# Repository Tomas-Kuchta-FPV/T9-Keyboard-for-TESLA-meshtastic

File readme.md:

# T9 Keyboard for TESLA meshtastic
> This is an experimental, low-polish project and without docs.  
It’s shared for reference and tinkering, not as a ready-to-build design.  
Proceed only if you’re comfortable filling in the gaps yourself.  

It's a sub part for an undocumented project that I'm calling TESLA meshtastic.  
Its main purpuse is to find out if a T9 style (4x3) keyboard can be used as a text input for meshtastic.  
The idea is boroved from Travel Buddy. As this idea still lies in my head.  
    
## TESLA meshtastic
Features:
- Speaker with volume control
- T9 style keyboard
- navigation button
- USB-A powered
- Eink?

## Arduino nano code
It should interface the 3x4 keyboard to I2C.

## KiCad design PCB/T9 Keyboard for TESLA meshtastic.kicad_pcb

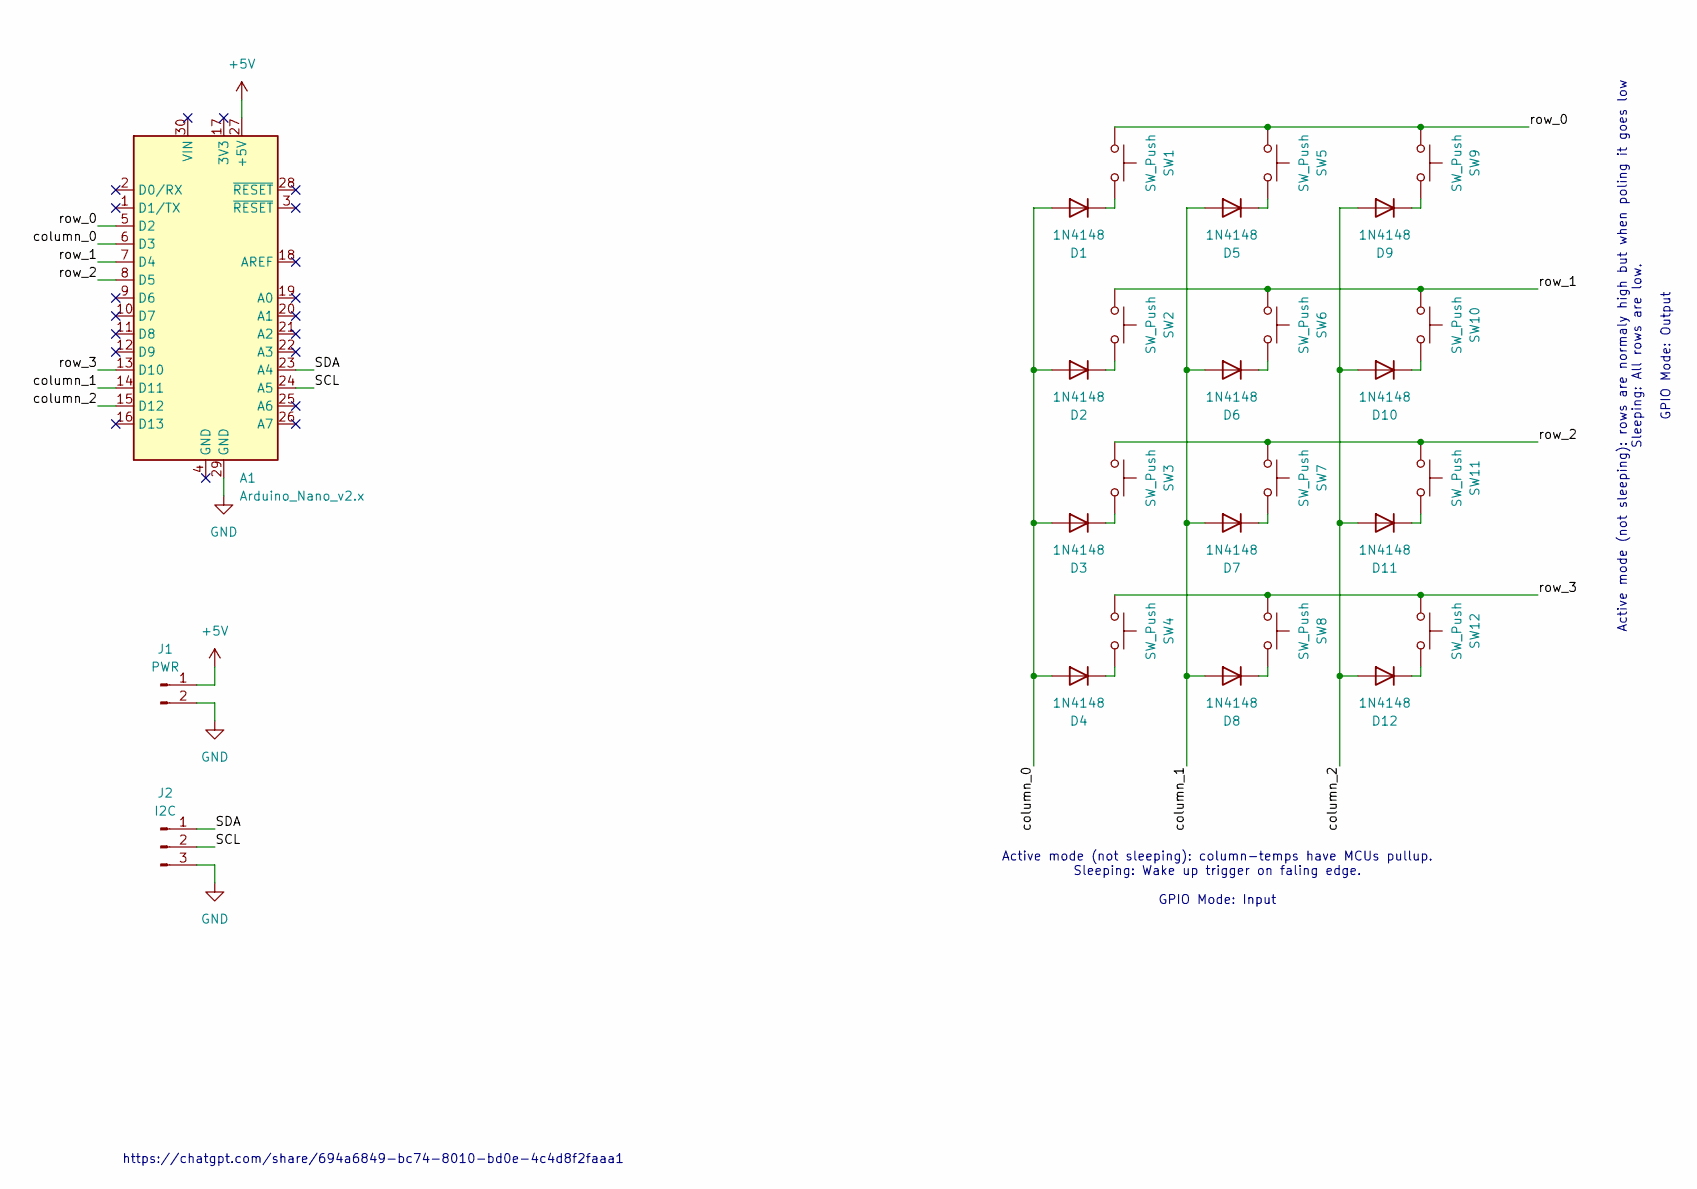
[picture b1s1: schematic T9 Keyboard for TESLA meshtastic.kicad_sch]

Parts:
A1: Arduino_Nano_v2.x; Arduino_Nano
D1, D2, D3, D4, D5, D6, D7, D8, D9, D10, D11, D12: 1N4148; D_DO-35_SOD27_P7.62mm_Horizontal; LCSC C60580
J1: PWR; PinSocket_1x02_P2.54mm_Vertical
J2: I2C; PinSocket_1x03_P2.54mm_Vertical
SW1, SW2, SW3, SW4, SW5, SW6, SW7, SW8, SW9, SW10, SW11, SW12: SW_Push; TESLA-3 FK 573 00; LCSC C318884

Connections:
+5V: A1.27 (+5V), J1.1
/SCL: A1.24 (A5), J2.2
/SDA: A1.23 (A4), J2.1
/column_0: A1.6 (D3), D1.2 (A), D2.2 (A), D3.2 (A), D4.2 (A)
/column_1: A1.14 (D11), D5.2 (A), D6.2 (A), D7.2 (A), D8.2 (A)
/column_2: A1.15 (D12), D9.2 (A), D10.2 (A), D11.2 (A), D12.2 (A)
/row_0: A1.5 (D2), SW1.1, SW5.1, SW9.1
/row_1: A1.7 (D4), SW2.1, SW6.1, SW10.1
/row_2: A1.8 (D5), SW3.1, SW7.1, SW11.1
/row_3: A1.13 (D10), SW4.1, SW8.1, SW12.1
GND: A1.29 (GND), J1.2, J2.3
unnamed: D1.1 (K), SW1.2
unnamed: D2.1 (K), SW2.2
unnamed: D3.1 (K), SW3.2
unnamed: D4.1 (K), SW4.2
unnamed: D5.1 (K), SW5.2
unnamed: D6.1 (K), SW6.2
unnamed: D7.1 (K), SW7.2
unnamed: D8.1 (K), SW8.2
unnamed: D9.1 (K), SW9.2
unnamed: D10.1 (K), SW10.2
unnamed: D11.1 (K), SW11.2
unnamed: D12.1 (K), SW12.2

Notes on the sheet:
https://chatgpt.com/share/694a6849-bc74-8010-bd0e-4c4d8f2faaa1
Active mode (not sleeping): rows are normaly high but when poling it goes low Sleeping: All rows are low. GPIO Mode: Output
Active mode (not sleeping): column-temps have MCUs pullup. Sleeping: Wake up trigger on faling edge. GPIO Mode: Input

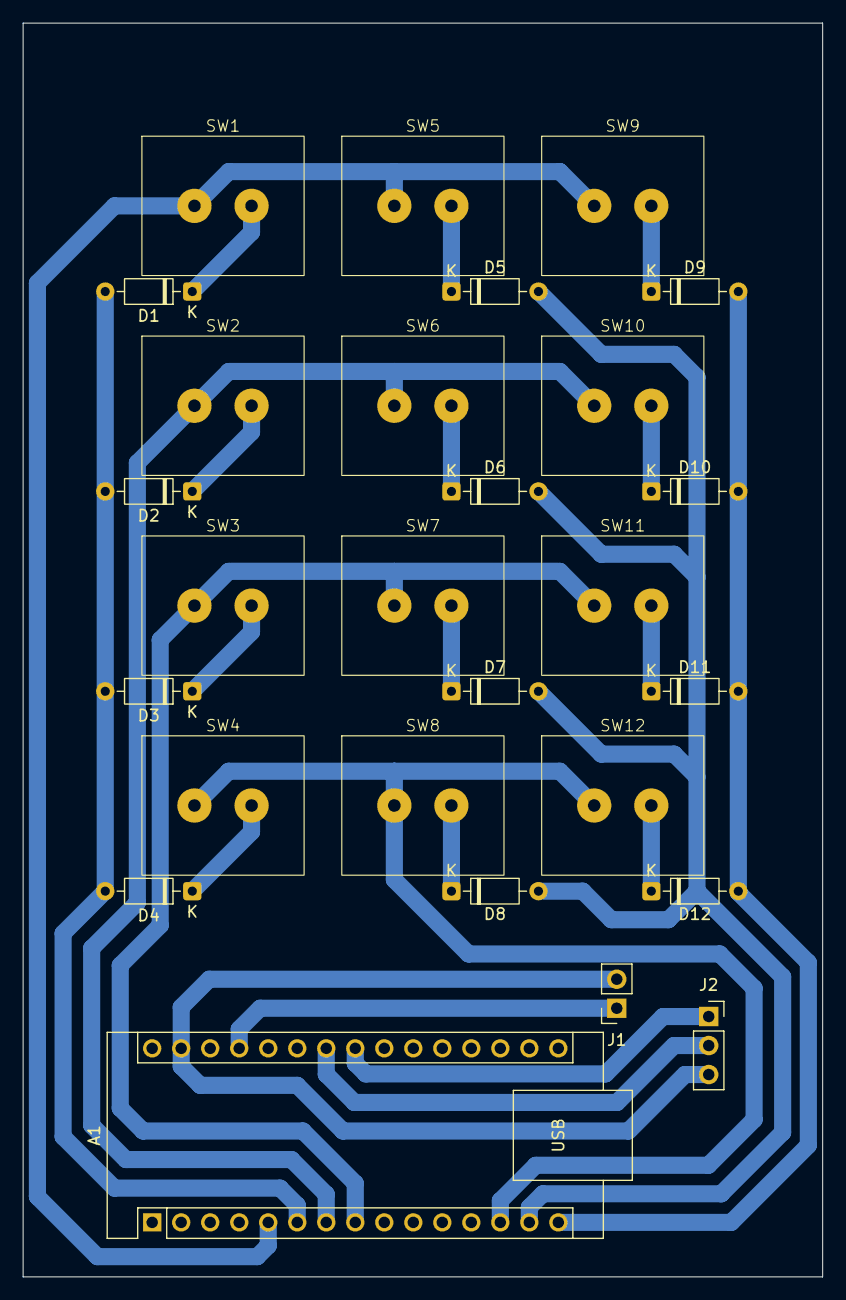
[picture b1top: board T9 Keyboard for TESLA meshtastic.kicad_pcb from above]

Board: 2 copper layers, 70.0 x 109.8 mm, 27 parts (0 on the bottom side), 23 nets.

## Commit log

2025-12-22 Drew up schematic.
2025-12-24 Finished the PCB.
2025-12-24 Readme
2026-01-13 Finished the PCB
2026-01-13 my code
2026-01-13 ChatGPT is working great.
2026-02-21 Vibecoded a wierd TCA8418 Keyboard implementation
